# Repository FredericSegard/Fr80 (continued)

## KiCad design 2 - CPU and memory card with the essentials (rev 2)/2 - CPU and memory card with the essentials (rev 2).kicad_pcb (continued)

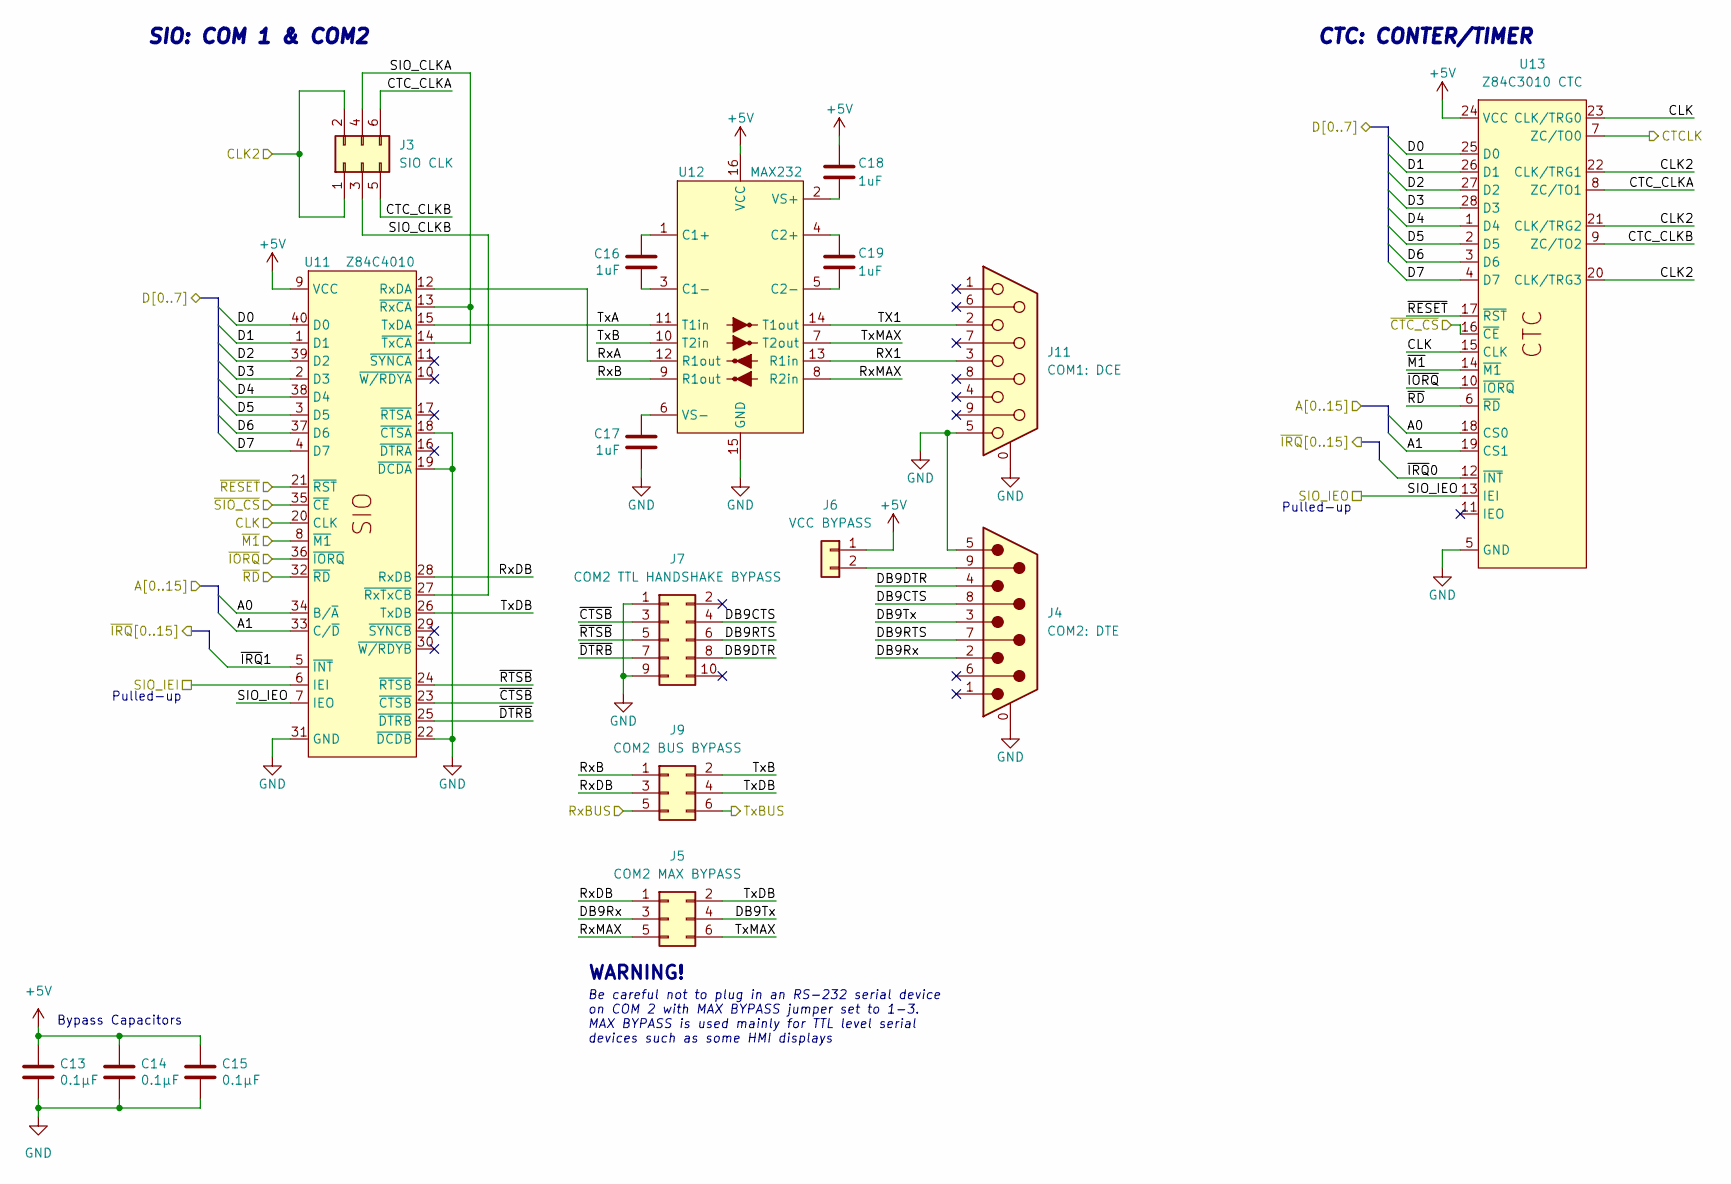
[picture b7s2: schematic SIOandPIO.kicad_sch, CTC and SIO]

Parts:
C13, C14, C15: 0.1µF; C_Disc_D3.0mm_W1.6mm_P2.50mm
C16, C17, C18, C19: 1uF; C_Disc_D3.0mm_W1.6mm_P2.50mm
J3: SIO CLK; PinHeader_2x03_P2.54mm_Vertical
J4: COM2: DTE; DSUB-9_Male_Horizontal_P2.77x2.84mm_EdgePinOffset4.94mm_Hou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
J5: COM2 MAX BYPASS; PinHeader_2x03_P2.54mm_Vertical
J6: VCC BYPASS; PinHeader_1x02_P2.54mm_Vertical
J7: COM2 TTL HANDSHAKE BYPASS; PinHeader_2x05_P2.54mm_Vertical
J9: COM2 BUS BYPASS; PinHeader_2x03_P2.54mm_Vertical
J11: COM1: DCE; DSUB-9_Female_Horizontal_P2.77x2.84mm_EdgePinOffset4.94mm_H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
U11: Z84C4010; DIP-40_W15.24mm_Socket
U12: MAX232; DIP-16_W7.62mm_Socket
U13: Z84C3010 CTC; DIP-28_W15.24mm_Socket

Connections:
+5V: C13.1, C14.1, C15.1, C18.1, J6.1, U11.9 (VCC), U12.16 (VCC), U13.24 (VCC); also elsewhere on the board
/A0: U11.34 (B/~A), U13.18 (CS0); also elsewhere on the board
/A1: U11.33 (C/~D), U13.19 (CS1); also elsewhere on the board
/CLK: U11.20 (CLK), U13.15 (CLK), U13.23 (CLK/TRG0); also elsewhere on the board
/CLK2: J3.1, J3.2, U13.20 (CLK/TRG3), U13.21 (CLK/TRG2), U13.22 (CLK/TRG1); also elsewhere on the board
/CTC and SIO/CTC_CLKA: J3.6, U13.8 (ZC/TO1)
/CTC and SIO/CTC_CLKB: J3.5, U13.9 (ZC/TO2)
/CTC and SIO/DB9CTS: J4.8, J7.4
/CTC and SIO/DB9DTR: J4.4, J7.8
/CTC and SIO/DB9RTS: J4.7, J7.6
/CTC and SIO/DB9Rx: J4.2, J5.3
/CTC and SIO/DB9Tx: J4.3, J5.4
/CTC and SIO/RX1: J11.3, U12.13 (R1in)
/CTC and SIO/RxA: U11.12 (RxDA), U12.12 (R1out)
/CTC and SIO/RxB: J9.1, U12.9 (R1out)
/CTC and SIO/RxDB: J5.1, J9.3, U11.28 (RxDB)
/CTC and SIO/RxMAX: J5.5, U12.8 (R2in)
/CTC and SIO/SIO_CLKA: J3.4, U11.13 (~RxCA), U11.14 (~TxCA)
/CTC and SIO/SIO_CLKB: J3.3, U11.27 (~RxTxCB)
/CTC and SIO/TX1: J11.2, U12.14 (T1out)
/CTC and SIO/TxA: U11.15 (TxDA), U12.11 (T1in)
/CTC and SIO/TxB: J9.2, U12.10 (T2in)
/CTC and SIO/TxDB: J5.2, J9.4, U11.26 (TxDB)
/CTC and SIO/TxMAX: J5.6, U12.7 (T2out)
/CTC and SIO/~CTSB: J7.3, U11.23 (~CTSB)
/CTC and SIO/~DTRB: J7.7, U11.25 (~DTRB)
/CTC and SIO/~RTSB: J7.5, U11.24 (~RTSB)
/CTCLK: U13.7 (ZC/TO0); also elsewhere on the board
/CTC_CS: U13.16 (~CE); also elsewhere on the board
/D0: U11.40 (D0), U13.25 (D0); also elsewhere on the board
/D1: U11.1 (D1), U13.26 (D1); also elsewhere on the board
/D2: U11.39 (D2), U13.27 (D2); also elsewhere on the board
/D3: U11.2 (D3), U13.28 (D3); also elsewhere on the board
/D4: U11.38 (D4), U13.1 (D4); also elsewhere on the board
/D5: U11.3 (D5), U13.2 (D5); also elsewhere on the board
/D6: U11.37 (D6), U13.3 (D6); also elsewhere on the board
/D7: U11.4 (D7), U13.4 (D7); also elsewhere on the board
/RX: J9.5; also elsewhere on the board
/SIO_CS: U11.35 (~CE); also elsewhere on the board
/SIO_IEI: U11.6 (IEI); also elsewhere on the board
/SIO_IEO: U11.7 (IEO), U13.13 (IEI); also elsewhere on the board
/TX: J9.6; also elsewhere on the board
/~IORQ: U11.36 (~IORQ), U13.10 (~IORQ); also elsewhere on the board
/~IRQ0: U13.12 (~INT); also elsewhere on the board
/~IRQ1: U11.5 (~INT); also elsewhere on the board
/~M1: U11.8 (~M1), U13.14 (~M1); also elsewhere on the board
/~RD: U11.32 (~RD), U13.6 (~RD); also elsewhere on the board
/~RESET: U11.21 (~RST), U13.17 (~RST); also elsewhere on the board
GND: C13.2, C14.2, C15.2, C17.2, J4.0 (PAD), J4.5, J7.1, J7.9, J11.0 (PAD), J11.5, U11.18 (~CTSA), U11.19 (~DCDA), U11.22 (~DCDB), U11.31 (GND), U12.15 (GND), U13.5 (GND); also elsewhere on the board
unnamed: J4.9, J6.2
unnamed: C16.1, U12.1 (C1+)
unnamed: C16.2, U12.3 (C1-)
unnamed: C19.1, U12.4 (C2+)
unnamed: C19.2, U12.5 (C2-)
unnamed: C18.2, U12.2 (VS+)
unnamed: C17.1, U12.6 (VS-)

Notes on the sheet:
Pulled-up
CTC: CONTER/TIMER
Be careful not to plug in an RS-232 serial device on COM 2 with MAX BYPASS jumper set to 1-3. MAX BYPASS is used mainly for TTL level serial devices such as some HMI displays
SIO: COM 1 & COM2
WARNING!
Bypass Capacitors

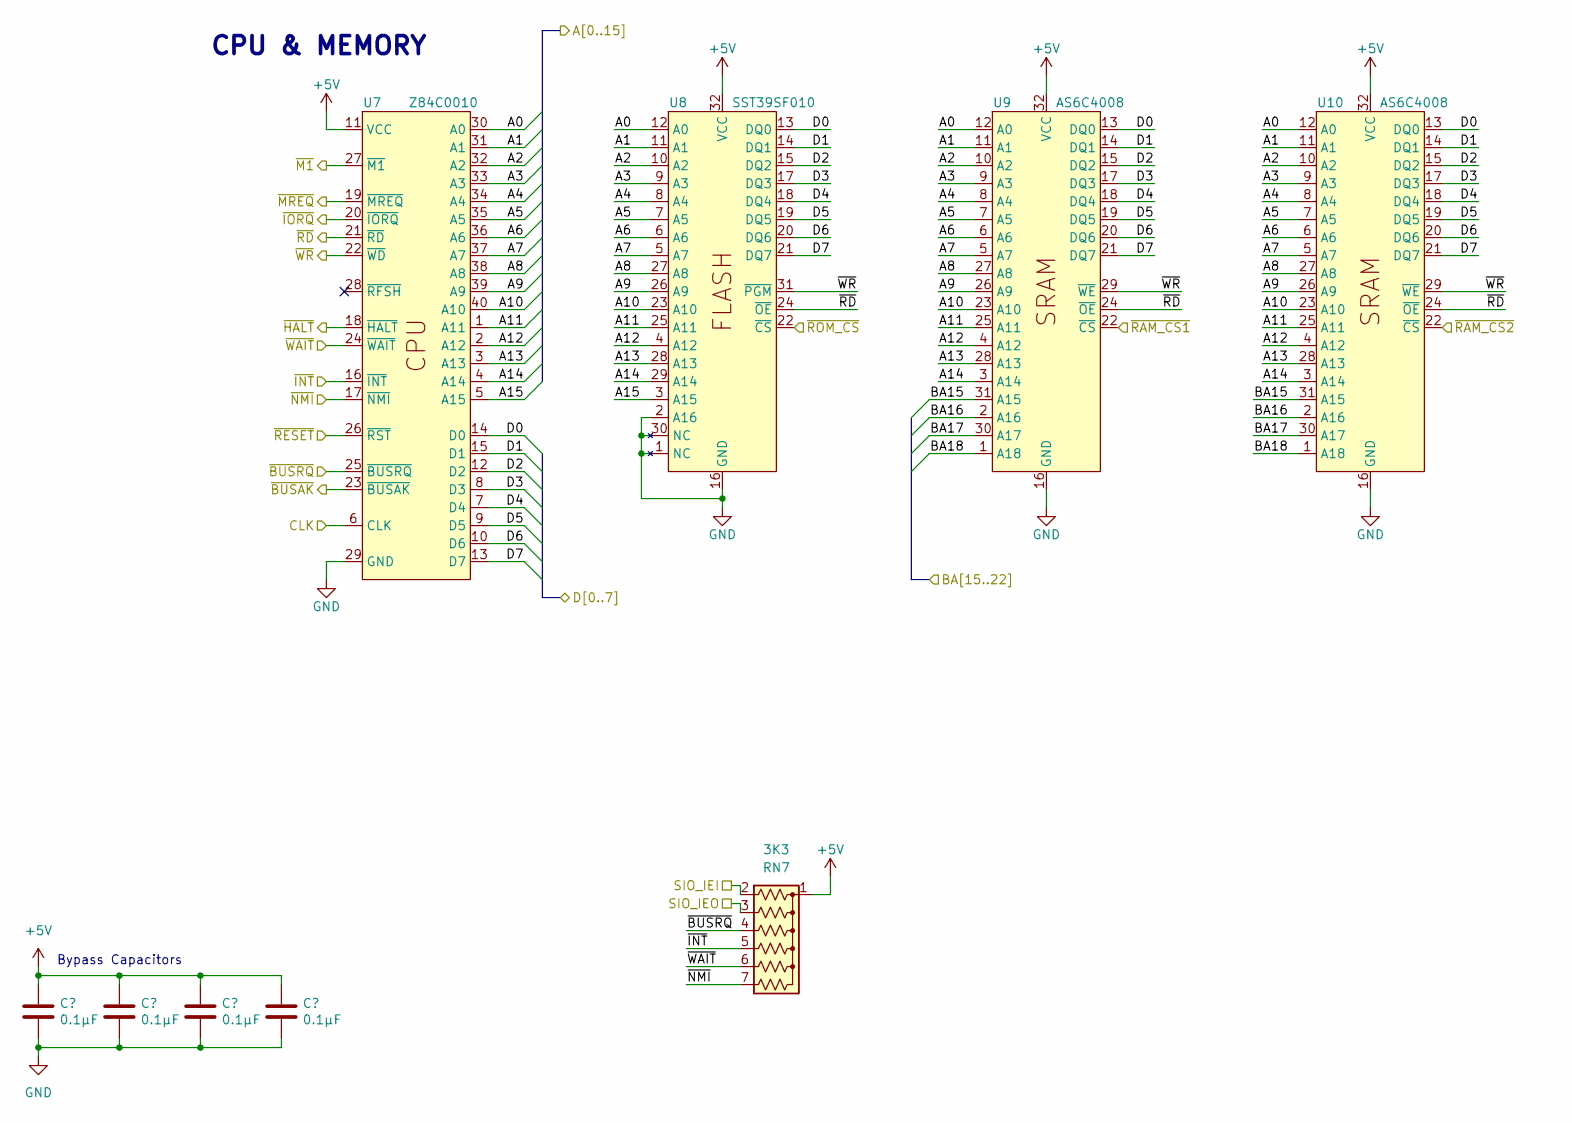
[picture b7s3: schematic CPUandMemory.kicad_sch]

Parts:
C10, C11, C12, C22: 0.1µF; C_Disc_D3.0mm_W1.6mm_P2.50mm
RN7: 3K3; R_Array_SIP7
U7: Z84C0010; DIP-40_W15.24mm_Socket
U8: SST39SF010; DIP_Socket-32_W11.9_W12.7_W15.24_W17.78_W18.5_3M_232-1285-0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
U9, U10: AS6C4008; DIP-32_W15.24mm_Socket

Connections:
+5V: C10.1, C11.1, C12.1, C22.1, RN7.1 (common), U7.11 (VCC), U8.32 (VCC), U9.32 (VCC), U10.32 (VCC); also elsewhere on the board
/A0: U7.30 (A0), U8.12 (A0), U9.12 (A0), U10.12 (A0); also elsewhere on the board
/A1: U7.31 (A1), U8.11 (A1), U9.11 (A1), U10.11 (A1); also elsewhere on the board
/A2: U7.32 (A2), U8.10 (A2), U9.10 (A2), U10.10 (A2); also elsewhere on the board
/A3: U7.33 (A3), U8.9 (A3), U9.9 (A3), U10.9 (A3); also elsewhere on the board
/A4: U7.34 (A4), U8.8 (A4), U9.8 (A4), U10.8 (A4); also elsewhere on the board
/A5: U7.35 (A5), U8.7 (A5), U9.7 (A5), U10.7 (A5); also elsewhere on the board
/A6: U7.36 (A6), U8.6 (A6), U9.6 (A6), U10.6 (A6); also elsewhere on the board
/A7: U7.37 (A7), U8.5 (A7), U9.5 (A7), U10.5 (A7); also elsewhere on the board
/A8: U7.38 (A8), U8.27 (A8), U9.27 (A8), U10.27 (A8); also elsewhere on the board
/A9: U7.39 (A9), U8.26 (A9), U9.26 (A9), U10.26 (A9); also elsewhere on the board
/A10: U7.40 (A10), U8.23 (A10), U9.23 (A10), U10.23 (A10); also elsewhere on the board
/A11: U7.1 (A11), U8.25 (A11), U9.25 (A11), U10.25 (A11); also elsewhere on the board
/A12: U7.2 (A12), U8.4 (A12), U9.4 (A12), U10.4 (A12); also elsewhere on the board
/A13: U7.3 (A13), U8.28 (A13), U9.28 (A13), U10.28 (A13); also elsewhere on the board
/A14: U7.4 (A14), U8.29 (A14), U9.3 (A14), U10.3 (A14); also elsewhere on the board
/A15: U7.5 (A15), U8.3 (A15); also elsewhere on the board
/BA15: U9.31 (A15), U10.31 (A15); also elsewhere on the board
/BA16: U9.2 (A16), U10.2 (A16); also elsewhere on the board
/BA17: U9.30 (A17), U10.30 (A17); also elsewhere on the board
/BA18: U9.1 (A18), U10.1 (A18); also elsewhere on the board
/CLK: U7.6 (CLK); also elsewhere on the board
/D0: U7.14 (D0), U8.13 (DQ0), U9.13 (DQ0), U10.13 (DQ0); also elsewhere on the board
/D1: U7.15 (D1), U8.14 (DQ1), U9.14 (DQ1), U10.14 (DQ1); also elsewhere on the board
/D2: U7.12 (D2), U8.15 (DQ2), U9.15 (DQ2), U10.15 (DQ2); also elsewhere on the board
/D3: U7.8 (D3), U8.17 (DQ3), U9.17 (DQ3), U10.17 (DQ3); also elsewhere on the board
/D4: U7.7 (D4), U8.18 (DQ4), U9.18 (DQ4), U10.18 (DQ4); also elsewhere on the board
/D5: U7.9 (D5), U8.19 (DQ5), U9.19 (DQ5), U10.19 (DQ5); also elsewhere on the board
/D6: U7.10 (D6), U8.20 (DQ6), U9.20 (DQ6), U10.20 (DQ6); also elsewhere on the board
/D7: U7.13 (D7), U8.21 (DQ7), U9.21 (DQ7), U10.21 (DQ7); also elsewhere on the board
/SIO_IEI: RN7.2 (R1); also elsewhere on the board
/SIO_IEO: RN7.3 (R2); also elsewhere on the board
/~BUSAK: U7.23 (~BUSAK); also elsewhere on the board
/~BUSRQ: RN7.4 (R3), U7.25 (~BUSRQ); also elsewhere on the board
/~HALT: U7.18 (~HALT); also elsewhere on the board
/~INT: RN7.5 (R4), U7.16 (~INT); also elsewhere on the board
/~IORQ: U7.20 (~IORQ); also elsewhere on the board
/~M1: U7.27 (~M1); also elsewhere on the board
/~MREQ: U7.19 (~MREQ); also elsewhere on the board
/~NMI: RN7.7 (R6), U7.17 (~NMI); also elsewhere on the board
/~RAM_CS1: U9.22 (~CS); also elsewhere on the board
/~RAM_CS2: U10.22 (~CS); also elsewhere on the board
/~RD: U7.21 (~RD), U8.24 (~OE), U9.24 (~OE), U10.24 (~OE); also elsewhere on the board
/~RESET: U7.26 (~RST); also elsewhere on the board
/~ROM_CS: U8.22 (~CS); also elsewhere on the board
/~WAIT: RN7.6 (R5), U7.24 (~WAIT); also elsewhere on the board
/~WR: U7.22 (~WD), U8.31 (~PGM), U9.29 (~WE), U10.29 (~WE); also elsewhere on the board
GND: C10.2, C11.2, C12.2, C22.2, U7.29 (GND), U8.1 (NC), U8.2 (A16), U8.16 (GND), U8.30 (NC), U9.16 (GND), U10.16 (GND); also elsewhere on the board

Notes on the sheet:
Bypass Capacitors
CPU & MEMORY

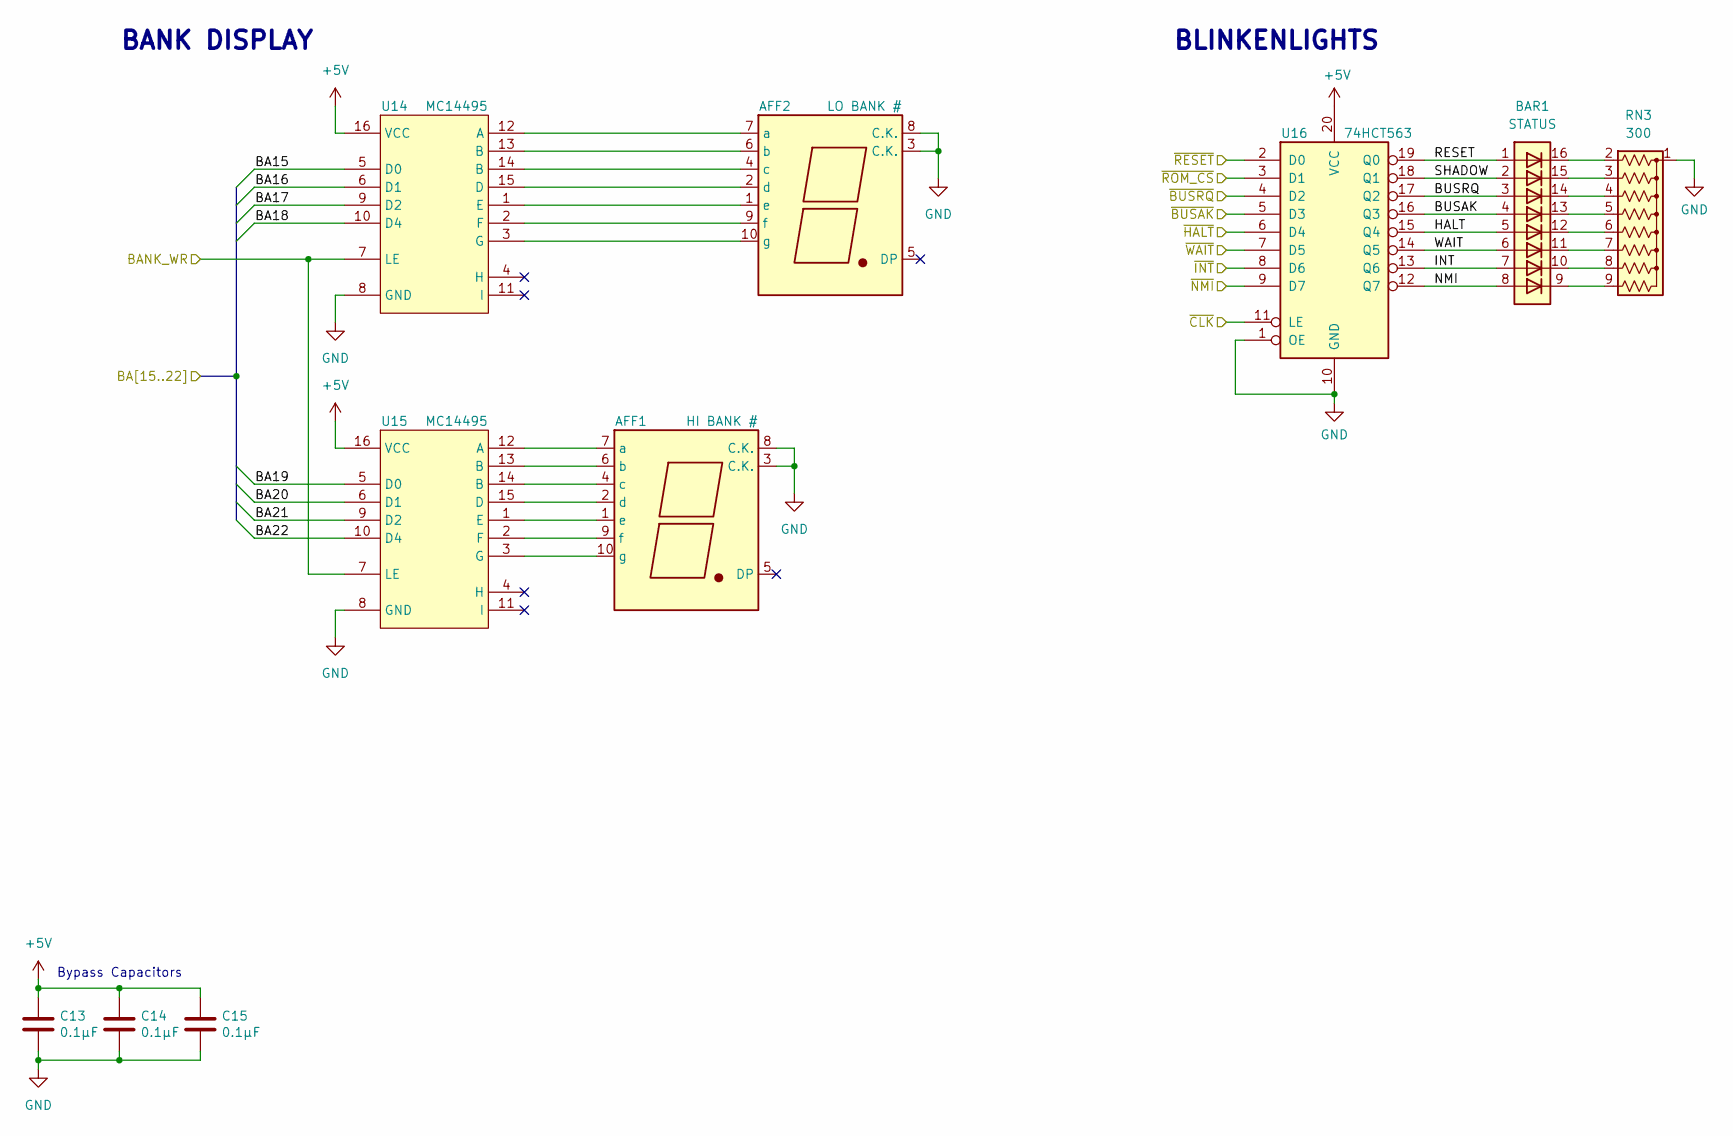
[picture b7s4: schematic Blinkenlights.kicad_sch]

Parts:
AFF1: HI BANK #; 7SegmentLED_LTS6760_LTS6780
AFF2: LO BANK #; 7SegmentLED_LTS6760_LTS6780
BAR1: STATUS; BAR_GRAPH_8
C13, C14, C15: 0.1µF; C_Disc_D3.0mm_W1.6mm_P2.50mm
RN3: 300; R_Array_SIP9
U14, U15: MC14495; DIP-16_W7.62mm_Socket
U16: 74HCT563; DIP-20_W7.62mm_Socket

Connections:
+5V: C13.1, C14.1, C15.1, U14.16 (VCC), U15.16 (VCC), U16.20 (VCC); also elsewhere on the board
/BA15: U14.5 (D0); also elsewhere on the board
/BA16: U14.6 (D1); also elsewhere on the board
/BA17: U14.9 (D2); also elsewhere on the board
/BA18: U14.10 (D4); also elsewhere on the board
/BA19: U15.5 (D0); also elsewhere on the board
/BA20: U15.6 (D1); also elsewhere on the board
/BA21: U15.9 (D2); also elsewhere on the board
/BA22: U15.10 (D4); also elsewhere on the board
/Blinkenlights/BANK_WR: U14.7 (LE), U15.7 (LE); also elsewhere on the board
/Blinkenlights/BUSAK: BAR1.4 (A), U16.16 (Q3)
/Blinkenlights/BUSRQ: BAR1.3 (A), U16.17 (Q2)
/Blinkenlights/HALT: BAR1.5 (A), U16.15 (Q4)
/Blinkenlights/INT: BAR1.7 (A), U16.13 (Q6)
/Blinkenlights/NMI: BAR1.8 (A), U16.12 (Q7)
/Blinkenlights/RESET: BAR1.1 (A), U16.19 (Q0)
/Blinkenlights/SHADOW: BAR1.2 (A), U16.18 (Q1)
/Blinkenlights/WAIT: BAR1.6 (A), U16.14 (Q5)
/~BUSAK: U16.5 (D3); also elsewhere on the board
/~BUSRQ: U16.4 (D2); also elsewhere on the board
/~CLK: U16.11 (LE); also elsewhere on the board
/~HALT: U16.6 (D4); also elsewhere on the board
/~INT: U16.8 (D6); also elsewhere on the board
/~NMI: U16.9 (D7); also elsewhere on the board
/~RESET: U16.2 (D0); also elsewhere on the board
/~ROM_CS: U16.3 (D1); also elsewhere on the board
/~WAIT: U16.7 (D5); also elsewhere on the board
GND: AFF1.3 (C.K.), AFF1.8 (C.K.), AFF2.3 (C.K.), AFF2.8 (C.K.), C13.2, C14.2, C15.2, RN3.1 (common), U14.8 (GND), U15.8 (GND), U16.1 (OE), U16.10 (GND); also elsewhere on the board
unnamed: AFF1.7 (a), U15.12 (A)
unnamed: AFF1.6 (b), U15.13 (B)
unnamed: AFF1.4 (c), U15.14 (B)
unnamed: AFF1.2 (d), U15.15 (D)
unnamed: AFF1.1 (e), U15.1 (E)
unnamed: AFF1.9 (f), U15.2 (F)
unnamed: AFF1.10 (g), U15.3 (G)
unnamed: AFF2.7 (a), U14.12 (A)
unnamed: AFF2.6 (b), U14.13 (B)
unnamed: AFF2.4 (c), U14.14 (B)
unnamed: AFF2.2 (d), U14.15 (D)
unnamed: AFF2.1 (e), U14.1 (E)
unnamed: AFF2.9 (f), U14.2 (F)
unnamed: AFF2.10 (g), U14.3 (G)
unnamed: BAR1.16 (K), RN3.2 (R1)
unnamed: BAR1.15 (K), RN3.3 (R2)
unnamed: BAR1.14 (K), RN3.4 (R3)
unnamed: BAR1.13 (K), RN3.5 (R4)
unnamed: BAR1.12 (K), RN3.6 (R5)
unnamed: BAR1.11 (K), RN3.7 (R6)
unnamed: BAR1.10 (A), RN3.8 (R7)
unnamed: BAR1.9 (A), RN3.9 (R8)

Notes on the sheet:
BLINKENLIGHTS
Bypass Capacitors
BANK DISPLAY

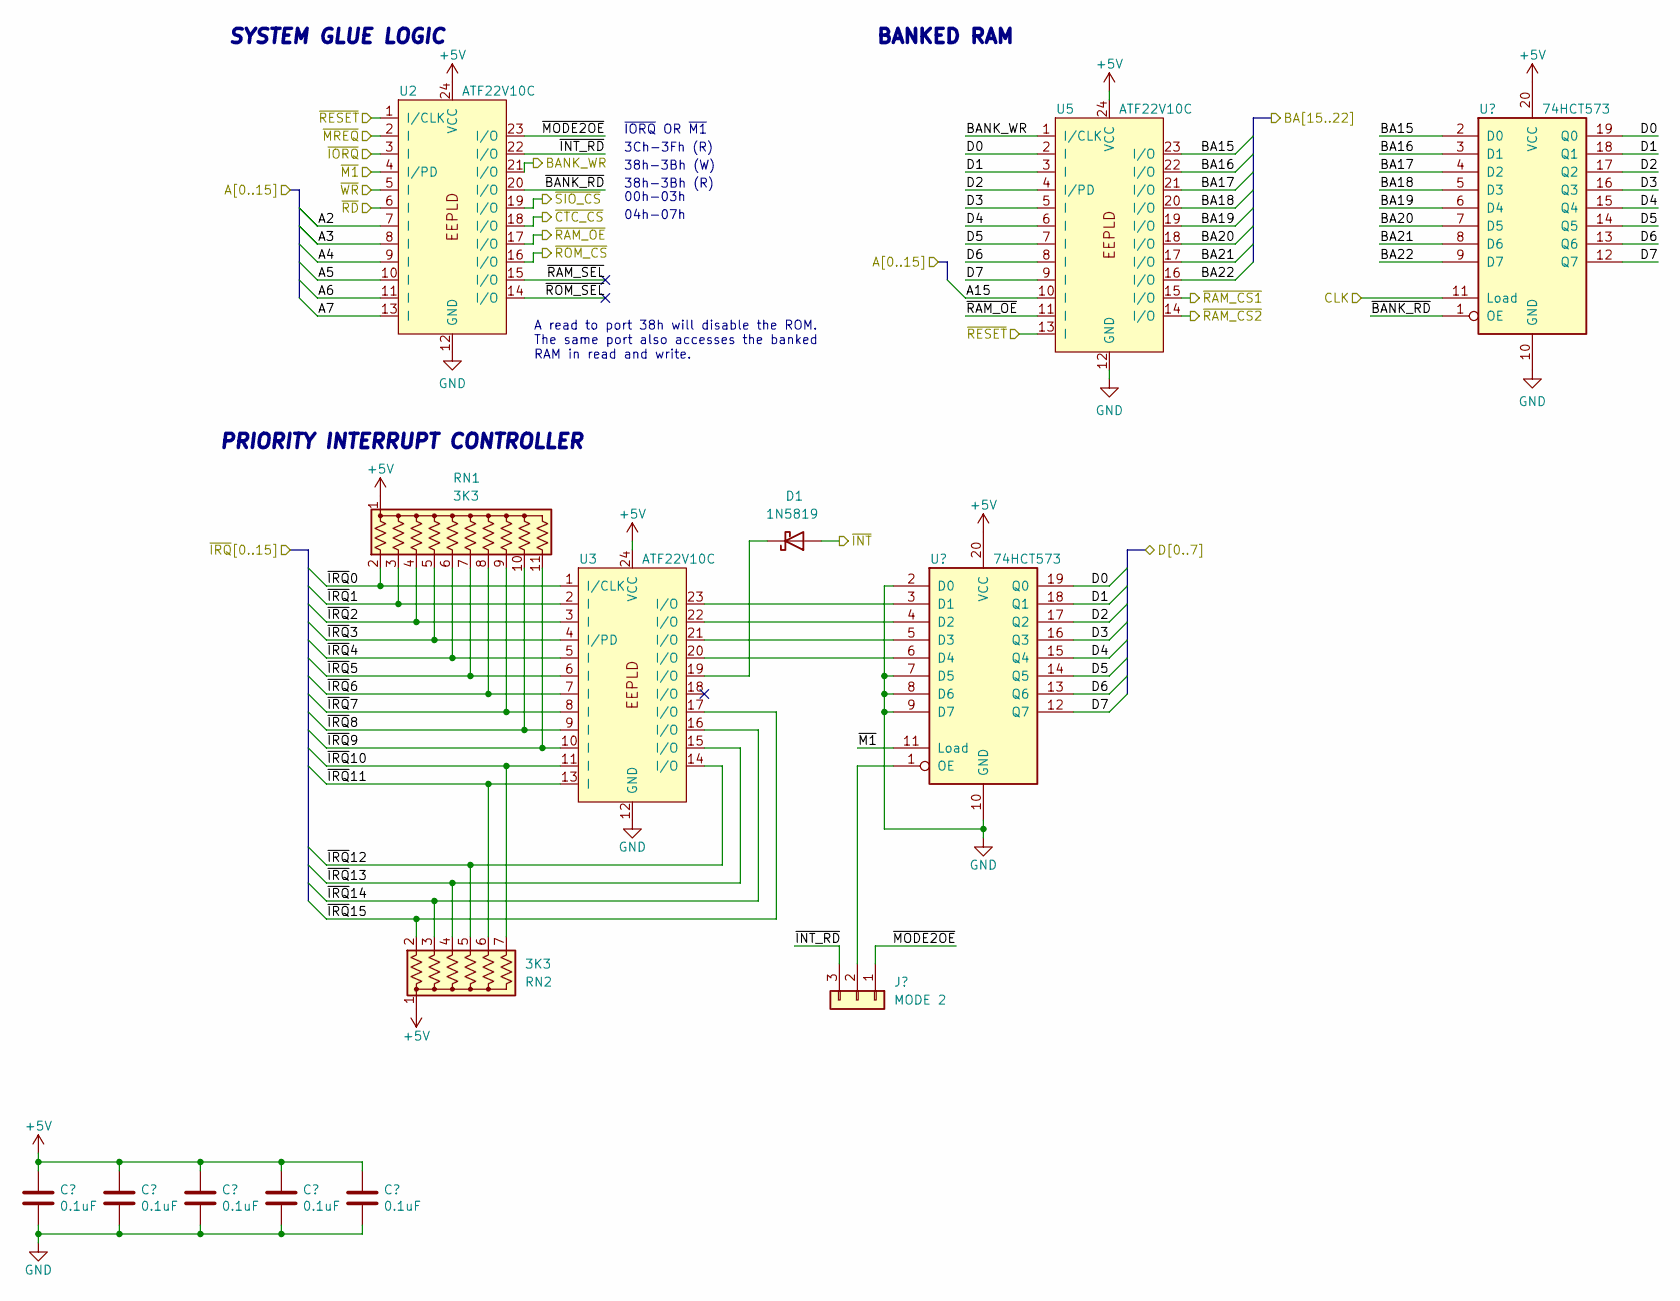
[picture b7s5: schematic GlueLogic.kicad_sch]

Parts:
C4, C5, C6, C7, C8: 0.1uF; C_Disc_D3.0mm_W2.0mm_P2.50mm
D1: 1N5819; D_DO-41_SOD81_P10.16mm_Horizontal
J2: MODE 2; PinHeader_1x03_P2.54mm_Vertical
RN1: 3K3; R_Array_SIP11
RN2: 3K3; R_Array_SIP7
U2, U3, U5: ATF22V10C; DIP-24_W7.62mm_Socket
U4, U6: 74HCT573; DIP-20_W7.62mm_Socket

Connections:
+5V: C4.1, C5.1, C6.1, C7.1, C8.1, RN1.1 (common), RN2.1 (common), U2.24 (VCC), U3.24 (VCC), U4.20 (VCC), U5.24 (VCC), U6.20 (VCC); also elsewhere on the board
/A2: U2.7 (I); also elsewhere on the board
/A3: U2.8 (I); also elsewhere on the board
/A4: U2.9 (I); also elsewhere on the board
/A5: U2.10 (I); also elsewhere on the board
/A6: U2.11 (I); also elsewhere on the board
/A7: U2.13 (I); also elsewhere on the board
/A15: U5.10 (I); also elsewhere on the board
/BA15: U5.23 (I/O), U6.2 (D0); also elsewhere on the board
/BA16: U5.22 (I/O), U6.3 (D1); also elsewhere on the board
/BA17: U5.21 (I/O), U6.4 (D2); also elsewhere on the board
/BA18: U5.20 (I/O), U6.5 (D3); also elsewhere on the board
/BA19: U5.19 (I/O), U6.6 (D4); also elsewhere on the board
/BA20: U5.18 (I/O), U6.7 (D5); also elsewhere on the board
/BA21: U5.17 (I/O), U6.8 (D6); also elsewhere on the board
/BA22: U5.16 (I/O), U6.9 (D7); also elsewhere on the board
/BANK_WR: U2.21 (I/O), U5.1 (I/CLK); also elsewhere on the board
/CLK: U6.11 (Load); also elsewhere on the board
/CTC_CS: U2.19 (I/O); also elsewhere on the board
/D0: U4.19 (Q0), U5.2 (I), U6.19 (Q0); also elsewhere on the board
/D1: U4.18 (Q1), U5.3 (I), U6.18 (Q1); also elsewhere on the board
/D2: U4.17 (Q2), U5.4 (I/PD), U6.17 (Q2); also elsewhere on the board
/D3: U4.16 (Q3), U5.5 (I), U6.16 (Q3); also elsewhere on the board
/D4: U4.15 (Q4), U5.6 (I), U6.15 (Q4); also elsewhere on the board
/D5: U4.14 (Q5), U5.7 (I), U6.14 (Q5); also elsewhere on the board
/D6: U4.13 (Q6), U5.8 (I), U6.13 (Q6); also elsewhere on the board
/D7: U4.12 (Q7), U5.9 (I), U6.12 (Q7); also elsewhere on the board
/Glue Logic/~BANK_RD: U2.20 (I/O), U6.1 (OE)
/Glue Logic/~INT_RD: J2.3, U2.22 (I/O)
/Glue Logic/~MODE2OE: J2.1, U2.23 (I/O)
/Glue Logic/~RAM_SEL: U2.15 (I/O)
/Glue Logic/~ROM_SEL: U2.14 (I/O)
/SIO_CS: U2.18 (I/O); also elsewhere on the board
/~BANK: U2.17 (I/O), U5.11 (I); also elsewhere on the board
/~INT: D1.2 (A); also elsewhere on the board
/~IORQ: U2.3 (I); also elsewhere on the board
/~IRQ0: RN1.2 (R1), U3.1 (I/CLK); also elsewhere on the board
/~IRQ1: RN1.3 (R2), U3.2 (I); also elsewhere on the board
/~IRQ2: RN1.4 (R3), U3.3 (I)
/~IRQ3: RN1.5 (R4), U3.4 (I/PD); also elsewhere on the board
/~IRQ4: RN1.6 (R5), U3.5 (I); also elsewhere on the board
/~IRQ5: RN1.7 (R6), U3.6 (I); also elsewhere on the board
/~IRQ6: RN1.8 (R7), U3.7 (I); also elsewhere on the board
/~IRQ7: RN1.9 (R8), U3.8 (I); also elsewhere on the board
/~IRQ8: RN1.10 (R9), U3.9 (I); also elsewhere on the board
/~IRQ9: RN1.11 (R10), U3.10 (I); also elsewhere on the board
/~IRQ10: RN2.7 (R6), U3.11 (I); also elsewhere on the board
/~IRQ11: RN2.6 (R5), U3.13 (I); also elsewhere on the board
/~IRQ12: RN2.5 (R4), U3.14 (I/O); also elsewhere on the board
/~IRQ13: RN2.4 (R3), U3.15 (I/O); also elsewhere on the board
/~IRQ14: RN2.3 (R2), U3.16 (I/O); also elsewhere on the board
/~IRQ15: RN2.2 (R1), U3.17 (I/O); also elsewhere on the board
/~M1: U2.4 (I/PD), U4.11 (Load); also elsewhere on the board
/~MREQ: U2.2 (I); also elsewhere on the board
/~RAM_CS1: U5.15 (I/O); also elsewhere on the board
/~RAM_CS2: U5.14 (I/O); also elsewhere on the board
/~RD: U2.6 (I); also elsewhere on the board
/~RESET: U2.1 (I/CLK), U5.13 (I); also elsewhere on the board
/~ROM_CS: U2.16 (I/O); also elsewhere on the board
/~WR: U2.5 (I); also elsewhere on the board
GND: C4.2, C5.2, C6.2, C7.2, C8.2, U2.12 (GND), U3.12 (GND), U4.2 (D0), U4.7 (D5), U4.8 (D6), U4.9 (D7), U4.10 (GND), U5.12 (GND), U6.10 (GND); also elsewhere on the board
unnamed: D1.1 (K), U3.19 (I/O)
unnamed: J2.2, U4.1 (OE)
unnamed: U3.23 (I/O), U4.3 (D1)
unnamed: U3.22 (I/O), U4.4 (D2)
unnamed: U3.21 (I/O), U4.5 (D3)
unnamed: U3.20 (I/O), U4.6 (D4)

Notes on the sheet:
PRIORITY INTERRUPT CONTROLLER
3Ch-3Fh (R)
SYSTEM GLUE LOGIC
00h-03h
~{IORQ} OR ~{M1}
38h-3Bh (W)
38h-3Bh (R)
04h-07h
BANKED RAM
A read to port 38h will disable the ROM. The same port also accesses the banked RAM in read and write.

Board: 2 copper layers, 58 parts (0 on the bottom side), 148 nets, no tracks yet.

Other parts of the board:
C9, C20, C21: 0.1µF; C_Disc_D3.0mm_W1.6mm_P2.50mm

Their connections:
+5V: C9.1, C20.1, C21.1; also elsewhere on the board
GND: C9.2, C20.2, C21.2; also elsewhere on the board

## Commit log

2023-08-15 First commit: Backplane almost finalized, and CPU & core peripherals card
    The backplane has some cleanup to be done with the PCB tracks. And I'm still in the process of designing the CPU with core peripherals card.
2023-08-15 Updated gitignore
2023-08-15 Cleaned up the PCB and ploted the gerber and schematic
2023-08-15 Added existing assembler code and PLD files
2023-08-16 Removed unessential components and added capacitors on the bus lanes. Still need work for on the silkscreen side.
2023-08-17 Finished the silkscreen and outputed the Gerber
2023-08-19 Work in progress... don't mind the mess! It will be cleaned up shortly.
2023-08-19 Minor tweaks to the backplane, and will be sending it out for manufacture
2023-08-21 Updated disk activity circuit in mother board, and improved layout in CPU card
2023-08-22 Trying to hash out the flaws
2023-08-24 Minor tweak
2023-08-26 Finally finalized the backplane to my liking.
2023-08-26 Added tear drops
2023-08-28 Finished the schematic. Laying out the board (WiP)
2023-08-29 Replacing a lot of TTL chips by 2 PLDs. Also, added blinkenlights.
2023-08-29 Removed rev1 from the repo. Keeping only rev2
2023-08-29 Updated the readme
2023-08-29 Added image of backplane to readme
2023-08-29 Cleaned up unnecessary files from the repo
2023-08-31 Added Interrupt Enable daisy chain jumpers between the ISA slots
2023-08-31 Finished component placement, currently routing.
2023-09-01 Testing a theory that I'm going to breadboard.
2023-09-03 Removed the alternate power input.
    The soft power on circuit was flaky upon testing.
2023-09-03 Adding buffers to the CPU card
2023-09-03 Updated the gerber to reflect the changes
2023-09-03 Removing unnecessary Spectra file
2023-09-03 Deleted unnecessary files
2023-09-03 Removed empty page
2023-09-03 Corrected spelling error
2023-09-03 Removed unbuffered rev 2 iteration. keeping only rev 2.1
2023-09-05 Trying to work out the PLD logic
2023-09-11 Changed lane labeling for IRQ0 and 1
2023-09-11 Starting a Forth interpreter (WiP)
2023-09-11 Still deciding on the components that will be on the core card.
2023-09-16 Finalized CPU card PCB for Fr80
2023-09-24 Updated gerber for backplane
2023-09-24 Archived rev 2.2 in favor of rev 3.
2023-09-24 Attempting to make my own Forth interpreter
2023-09-24 Compacted board to 100mm² PCB, where rev 2.2 was much bigger
2023-11-16 default to 2nd SIO
